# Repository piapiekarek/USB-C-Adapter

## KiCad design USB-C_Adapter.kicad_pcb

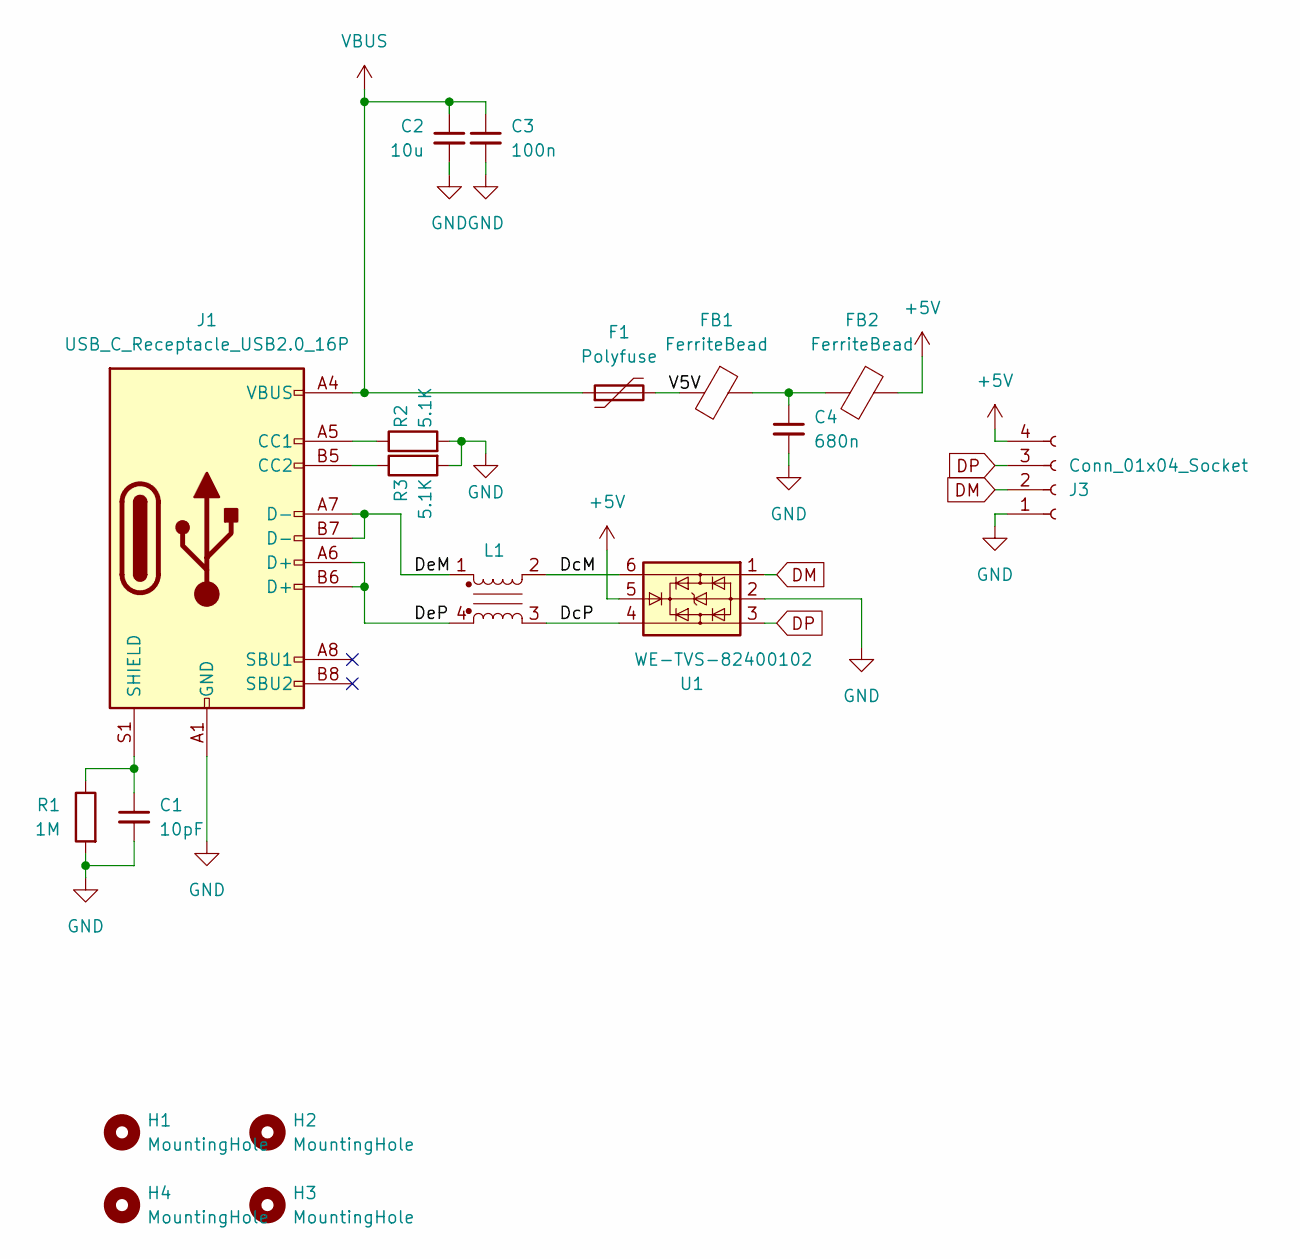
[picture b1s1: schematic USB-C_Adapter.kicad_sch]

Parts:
C1: 10pF; C_0402_1005Metric_Pad0.74x0.62mm_HandSolder
C2: 10u; C_0402_1005Metric_Pad0.74x0.62mm_HandSolder
C3: 100n; C_0402_1005Metric_Pad0.74x0.62mm_HandSolder
C4: 680n; C_0402_1005Metric_Pad0.74x0.62mm_HandSolder
F1: Polyfuse; C_0805_2012Metric_Pad1.18x1.45mm_HandSolder
FB1, FB2: FerriteBead; C_0201_0603Metric_Pad0.64x0.40mm_HandSolder
H1, H2, H3, H4: MountingHole; MountingHole_2.2mm_M2
J1: USB_C_Receptacle_USB2.0_16P; USB_C_Receptacle_Bottom_Up SMD
J3: Conn_01x04_Socket; JST_PH_S4B-PH-K_1x04_P2.00mm_Horizontal
L1: Choke_Wurth_WE-CNSW_744232090; L_CommonMode_Wurth_WE-CNSW-1206
R1: 1M; C_0402_1005Metric_Pad0.74x0.62mm_HandSolder
R2, R3: 5.1K; C_0402_1005Metric_Pad0.74x0.62mm_HandSolder
U1: WE-TVS-82400102; SOT-23-6

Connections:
+5V: FB2.1, J3.4, U1.5
/DcM: L1.2, U1.6
/DcP: L1.3, U1.4
/DeM: J1.A7 (D-), J1.B7 (D-), L1.1
/DeP: J1.A6 (D+), J1.B6 (D+), L1.4
/V5V: F1.2, FB1.2
DM: J3.2, U1.1
DP: J3.3, U1.3
GND: C1.2, C2.2, C3.2, C4.2, J1.A1 (GND), J1.A12 (GND), J1.B1 (GND), J1.B12 (GND), J3.1, R1.2, R2.2, R3.2, U1.2
unnamed: C4.1, FB1.1, FB2.2
unnamed: J1.A5 (CC1), R2.1
unnamed: J1.B5 (CC2), R3.1
unnamed: C1.1, J1.S1 (SHIELD), R1.1
VBUS: C2.1, C3.1, F1.1, J1.A4 (VBUS), J1.A9 (VBUS), J1.B4 (VBUS), J1.B9 (VBUS)

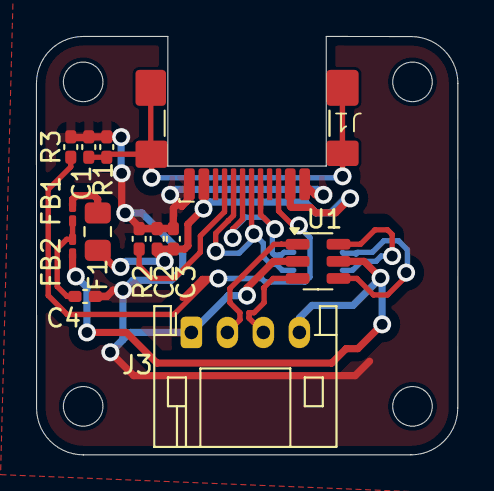
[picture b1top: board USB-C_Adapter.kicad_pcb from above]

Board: 2 copper layers, 23.4 x 23.2 mm, 18 parts (1 on the bottom side), 14 nets.

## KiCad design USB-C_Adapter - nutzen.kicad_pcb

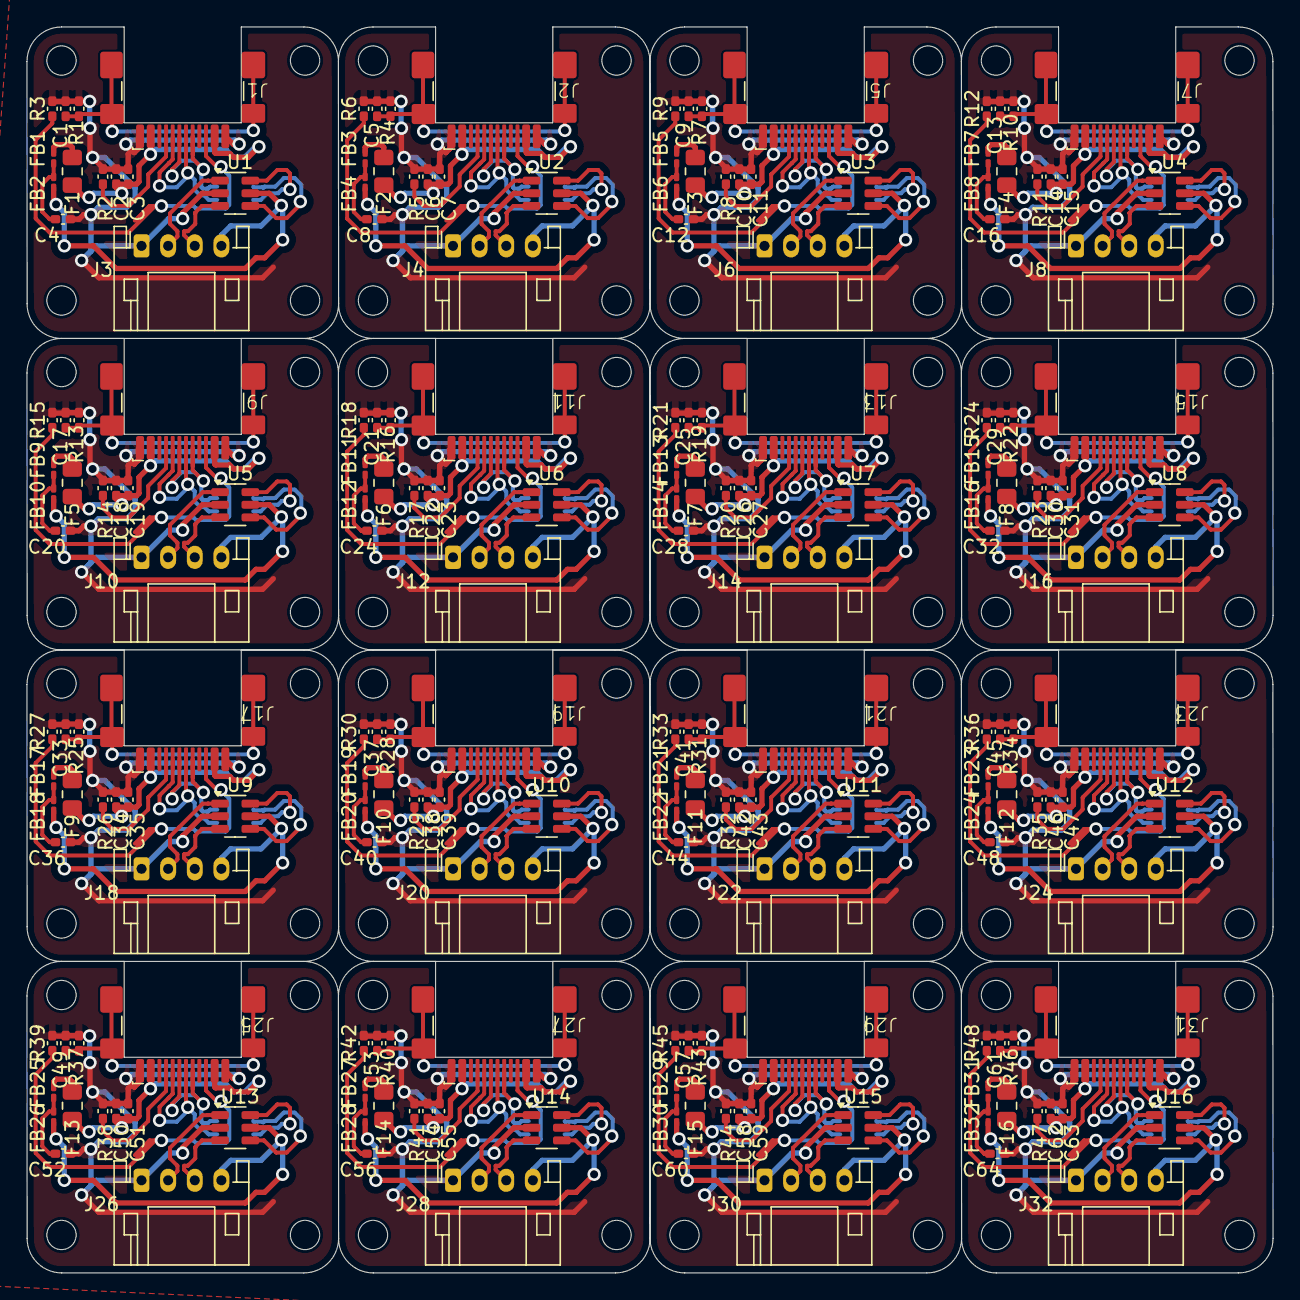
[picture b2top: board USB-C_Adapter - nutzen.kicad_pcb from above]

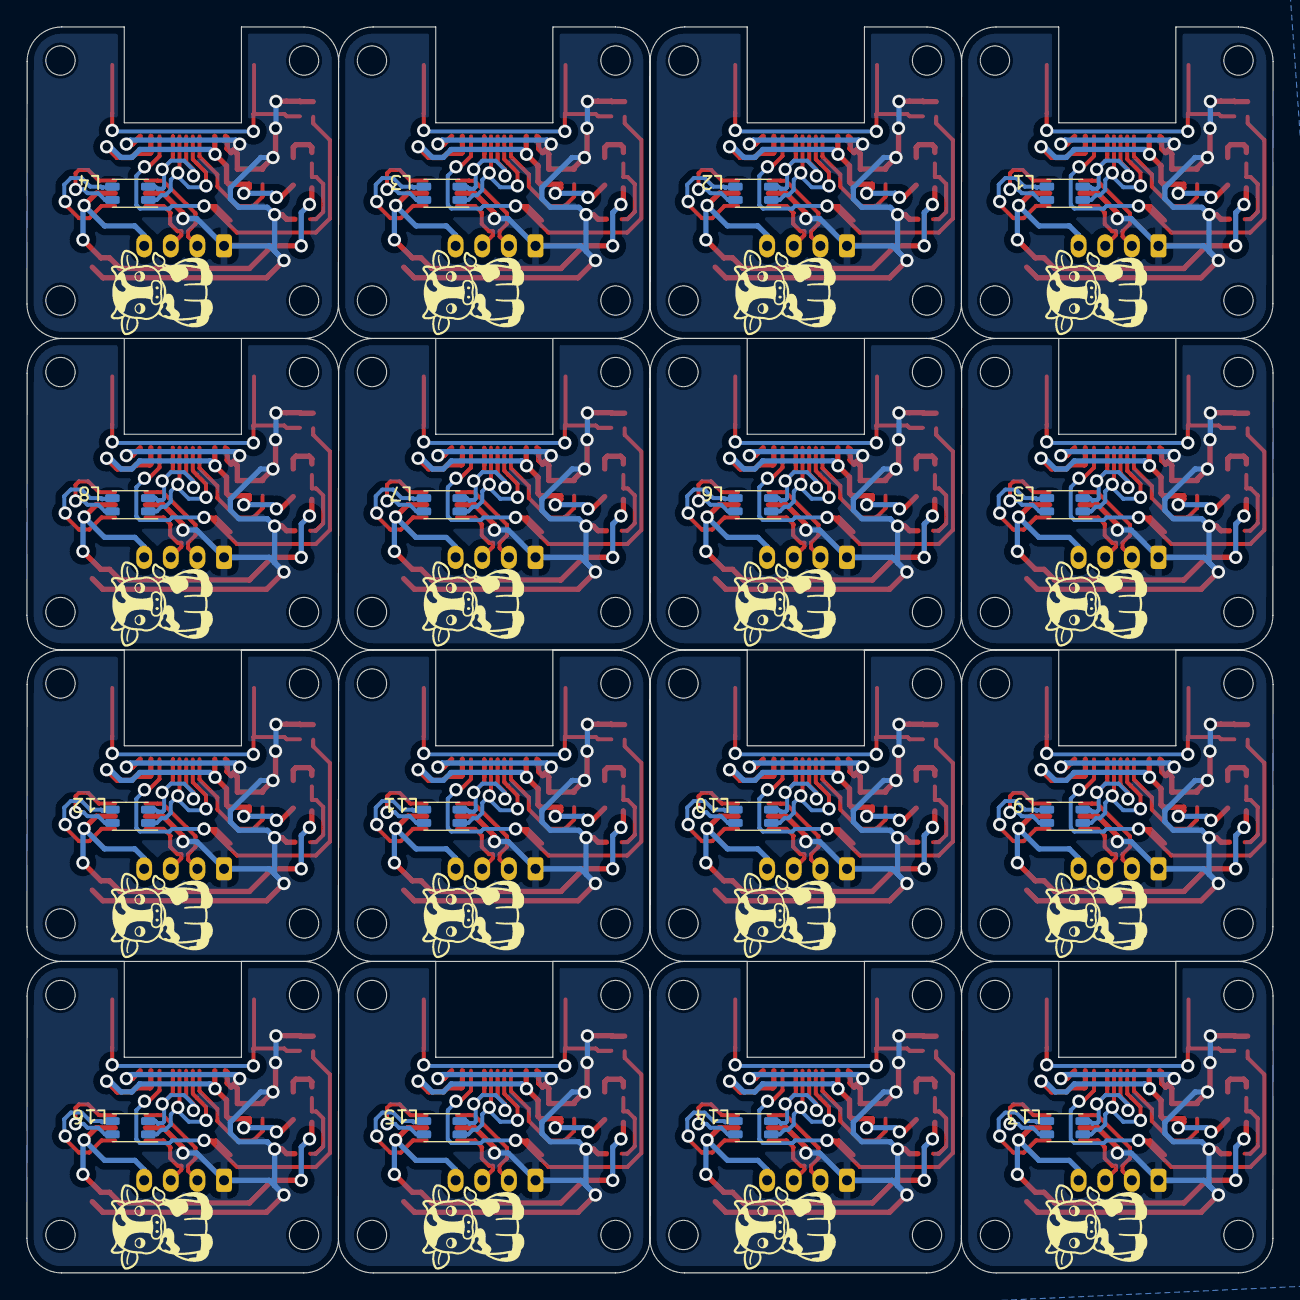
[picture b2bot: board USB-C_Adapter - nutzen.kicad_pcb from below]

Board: 2 copper layers, 93.6 x 93.6 mm, 288 parts (16 on the bottom side), 14 nets.

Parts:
C1, C5, C9, C13, C17, C21, C25, C29, C33, C37, C41, C45, C49, C53, C57, C61: 10pF; C_0402_1005Metric_Pad0.74x0.62mm_HandSolder
C2, C6, C10, C14, C18, C22, C26, C30, C34, C38, C42, C46, C50, C54, C58, C62: 10u; C_0402_1005Metric_Pad0.74x0.62mm_HandSolder
C3, C7, C11, C15, C19, C23, C27, C31, C35, C39, C43, C47, C51, C55, C59, C63: 100n; C_0402_1005Metric_Pad0.74x0.62mm_HandSolder
C4, C8, C12, C16, C20, C24, C28, C32, C36, C40, C44, C48, C52, C56, C60, C64: 680n; C_0402_1005Metric_Pad0.74x0.62mm_HandSolder
F1, F2, F3, F4, F5, F6, F7, F8, F9, F10, F11, F12, F13, F14, F15, F16: Polyfuse; C_0805_2012Metric_Pad1.18x1.45mm_HandSolder
FB1, FB2, FB3, FB4, FB5, FB6, FB7, FB8, FB9, FB10, FB11, FB12, FB13, FB14, FB15, FB16, FB17, FB18, FB19, FB20, FB21, FB22, FB23, FB24, FB25, FB26, FB27, FB28, FB29, FB30, FB31, FB32: FerriteBead; C_0201_0603Metric_Pad0.64x0.40mm_HandSolder
H1, H2, H3, H4, H5, H6, H7, H8, H9, H10, H11, H12, H13, H14, H15, H16, H17, H18, H19, H20, H21, H22, H23, H24, H25, H26, H27, H28, H29, H30, H31, H32, H33, H34, H35, H36, H37, H38, H39, H40, H41, H42, H43, H44, H45, H46, H47, H48, H49, H50, H51, H52, H53, H54, H55, H56, H57, H58, H59, H60, H61, H62, H63, H64: MountingHole; MountingHole_2.2mm_M2
J1, J2, J5, J7, J9, J11, J13, J15, J17, J19, J21, J23, J25, J27, J29, J31: USB_C_Receptacle_USB2.0_16P; USB_C_Receptacle_Bottom_Up SMD
J3, J4, J6, J8, J10, J12, J14, J16, J18, J20, J22, J24, J26, J28, J30, J32: Conn_01x04_Socket; JST_PH_S4B-PH-K_1x04_P2.00mm_Horizontal
L1, L2, L3, L4, L5, L6, L7, L8, L9, L10, L11, L12, L13, L14, L15, L16: Choke_Wurth_WE-CNSW_744232090; L_CommonMode_Wurth_WE-CNSW-1206
R1, R4, R7, R10, R13, R16, R19, R22, R25, R28, R31, R34, R37, R40, R43, R46: 1M; C_0402_1005Metric_Pad0.74x0.62mm_HandSolder
R2, R3, R5, R6, R8, R9, R11, R12, R14, R15, R17, R18, R20, R21, R23, R24, R26, R27, R29, R30, R32, R33, R35, R36, R38, R39, R41, R42, R44, R45, R47, R48: 5.1K; C_0402_1005Metric_Pad0.74x0.62mm_HandSolder
U1, U2, U3, U4, U5, U6, U7, U8, U9, U10, U11, U12, U13, U14, U15, U16: WE-TVS-82400102; SOT-23-6

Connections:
+5V: FB2.1, FB4.1, FB6.1, FB8.1, FB10.1, FB12.1, FB14.1, FB16.1, FB18.1, FB20.1, FB22.1, FB24.1, FB26.1, FB28.1, FB30.1, FB32.1, J3.4, J4.4, J6.4, J8.4, J10.4, J12.4, J14.4, J16.4, J18.4, J20.4, J22.4, J24.4, J26.4, J28.4, J30.4, J32.4, U1.5, U2.5, U3.5, U4.5, U5.5, U6.5, U7.5, U8.5, U9.5, U10.5, U11.5, U12.5, U13.5, U14.5, U15.5, U16.5
/DcM: L1.2, L2.2, L3.2, L4.2, L5.2, L6.2, L7.2, L8.2, L9.2, L10.2, L11.2, L12.2, L13.2, L14.2, L15.2, L16.2, U1.6, U2.6, U3.6, U4.6, U5.6, U6.6, U7.6, U8.6, U9.6, U10.6, U11.6, U12.6, U13.6, U14.6, U15.6, U16.6
/DcP: L1.3, L2.3, L3.3, L4.3, L5.3, L6.3, L7.3, L8.3, L9.3, L10.3, L11.3, L12.3, L13.3, L14.3, L15.3, L16.3, U1.4, U2.4, U3.4, U4.4, U5.4, U6.4, U7.4, U8.4, U9.4, U10.4, U11.4, U12.4, U13.4, U14.4, U15.4, U16.4
/DeM: J1.A7 (D-), J1.B7 (D-), J2.A7 (D-), J2.B7 (D-), J5.A7 (D-), J5.B7 (D-), J7.A7 (D-), J7.B7 (D-), J9.A7 (D-), J9.B7 (D-), J11.A7 (D-), J11.B7 (D-), J13.A7 (D-), J13.B7 (D-), J15.A7 (D-), J15.B7 (D-), J17.A7 (D-), J17.B7 (D-), J19.A7 (D-), J19.B7 (D-), J21.A7 (D-), J21.B7 (D-), J23.A7 (D-), J23.B7 (D-), J25.A7 (D-), J25.B7 (D-), J27.A7 (D-), J27.B7 (D-), J29.A7 (D-), J29.B7 (D-), J31.A7 (D-), J31.B7 (D-), L1.1, L2.1, L3.1, L4.1, L5.1, L6.1, L7.1, L8.1, L9.1, L10.1, L11.1, L12.1, L13.1, L14.1, L15.1, L16.1
/DeP: J1.A6 (D+), J1.B6 (D+), J2.A6 (D+), J2.B6 (D+), J5.A6 (D+), J5.B6 (D+), J7.A6 (D+), J7.B6 (D+), J9.A6 (D+), J9.B6 (D+), J11.A6 (D+), J11.B6 (D+), J13.A6 (D+), J13.B6 (D+), J15.A6 (D+), J15.B6 (D+), J17.A6 (D+), J17.B6 (D+), J19.A6 (D+), J19.B6 (D+), J21.A6 (D+), J21.B6 (D+), J23.A6 (D+), J23.B6 (D+), J25.A6 (D+), J25.B6 (D+), J27.A6 (D+), J27.B6 (D+), J29.A6 (D+), J29.B6 (D+), J31.A6 (D+), J31.B6 (D+), L1.4, L2.4, L3.4, L4.4, L5.4, L6.4, L7.4, L8.4, L9.4, L10.4, L11.4, L12.4, L13.4, L14.4, L15.4, L16.4
/V5V: F1.2, F2.2, F3.2, F4.2, F5.2, F6.2, F7.2, F8.2, F9.2, F10.2, F11.2, F12.2, F13.2, F14.2, F15.2, F16.2, FB1.2, FB3.2, FB5.2, FB7.2, FB9.2, FB11.2, FB13.2, FB15.2, FB17.2, FB19.2, FB21.2, FB23.2, FB25.2, FB27.2, FB29.2, FB31.2
DM: J3.2, J4.2, J6.2, J8.2, J10.2, J12.2, J14.2, J16.2, J18.2, J20.2, J22.2, J24.2, J26.2, J28.2, J30.2, J32.2, U1.1, U2.1, U3.1, U4.1, U5.1, U6.1, U7.1, U8.1, U9.1, U10.1, U11.1, U12.1, U13.1, U14.1, U15.1, U16.1
DP: J3.3, J4.3, J6.3, J8.3, J10.3, J12.3, J14.3, J16.3, J18.3, J20.3, J22.3, J24.3, J26.3, J28.3, J30.3, J32.3, U1.3, U2.3, U3.3, U4.3, U5.3, U6.3, U7.3, U8.3, U9.3, U10.3, U11.3, U12.3, U13.3, U14.3, U15.3, U16.3
GND: C1.2, C2.2, C3.2, C4.2, C5.2, C6.2, C7.2, C8.2, C9.2, C10.2, C11.2, C12.2, C13.2, C14.2, C15.2, C16.2, C17.2, C18.2, C19.2, C20.2, C21.2, C22.2, C23.2, C24.2, C25.2, C26.2, C27.2, C28.2, C29.2, C30.2, C31.2, C32.2, C33.2, C34.2, C35.2, C36.2, C37.2, C38.2, C39.2, C40.2, C41.2, C42.2, C43.2, C44.2, C45.2, C46.2, C47.2, C48.2, C49.2, C50.2, C51.2, C52.2, C53.2, C54.2, C55.2, C56.2, C57.2, C58.2, C59.2, C60.2, C61.2, C62.2, C63.2, C64.2, J1.A1 (GND), J1.A12 (GND), J1.B1 (GND), J1.B12 (GND), J2.A1 (GND), J2.A12 (GND), J2.B1 (GND), J2.B12 (GND), J3.1, J4.1, J5.A1 (GND), J5.A12 (GND), J5.B1 (GND), J5.B12 (GND), J6.1, J7.A1 (GND), J7.A12 (GND), J7.B1 (GND), J7.B12 (GND), J8.1, J9.A1 (GND), J9.A12 (GND), J9.B1 (GND), J9.B12 (GND), J10.1, J11.A1 (GND), J11.A12 (GND), J11.B1 (GND), J11.B12 (GND), J12.1, J13.A1 (GND), J13.A12 (GND), J13.B1 (GND), J13.B12 (GND), J14.1, J15.A1 (GND), J15.A12 (GND), J15.B1 (GND), J15.B12 (GND), J16.1, J17.A1 (GND), J17.A12 (GND), J17.B1 (GND), J17.B12 (GND), J18.1, J19.A1 (GND), J19.A12 (GND), J19.B1 (GND), J19.B12 (GND), J20.1, J21.A1 (GND), J21.A12 (GND), J21.B1 (GND), J21.B12 (GND), J22.1, J23.A1 (GND), J23.A12 (GND), J23.B1 (GND), J23.B12 (GND), J24.1, J25.A1 (GND), J25.A12 (GND), J25.B1 (GND), J25.B12 (GND), J26.1, J27.A1 (GND), J27.A12 (GND), J27.B1 (GND), J27.B12 (GND), J28.1, J29.A1 (GND), J29.A12 (GND), J29.B1 (GND), J29.B12 (GND), J30.1, J31.A1 (GND), J31.A12 (GND), J31.B1 (GND), J31.B12 (GND), J32.1, R1.2, R2.2, R3.2, R4.2, R5.2, R6.2, R7.2, R8.2, R9.2, R10.2, R11.2, R12.2, R13.2, R14.2, R15.2, R16.2, R17.2, R18.2, R19.2, R20.2, R21.2, R22.2, R23.2, R24.2, R25.2, R26.2, R27.2, R28.2, R29.2, R30.2, R31.2, R32.2, R33.2, R34.2, R35.2, R36.2, R37.2, R38.2, R39.2, R40.2, R41.2, R42.2, R43.2, R44.2, R45.2, R46.2, R47.2, R48.2, U1.2, U2.2, U3.2, U4.2, U5.2, U6.2, U7.2, U8.2, U9.2, U10.2, U11.2, U12.2, U13.2, U14.2, U15.2, U16.2
unnamed: C4.1, C8.1, C12.1, C16.1, C20.1, C24.1, C28.1, C32.1, C36.1, C40.1, C44.1, C48.1, C52.1, C56.1, C60.1, C64.1, FB1.1, FB2.2, FB3.1, FB4.2, FB5.1, FB6.2, FB7.1, FB8.2, FB9.1, FB10.2, FB11.1, FB12.2, FB13.1, FB14.2, FB15.1, FB16.2, FB17.1, FB18.2, FB19.1, FB20.2, FB21.1, FB22.2, FB23.1, FB24.2, FB25.1, FB26.2, FB27.1, FB28.2, FB29.1, FB30.2, FB31.1, FB32.2
unnamed: J1.A5 (CC1), J2.A5 (CC1), J5.A5 (CC1), J7.A5 (CC1), J9.A5 (CC1), J11.A5 (CC1), J13.A5 (CC1), J15.A5 (CC1), J17.A5 (CC1), J19.A5 (CC1), J21.A5 (CC1), J23.A5 (CC1), J25.A5 (CC1), J27.A5 (CC1), J29.A5 (CC1), J31.A5 (CC1), R2.1, R5.1, R8.1, R11.1, R14.1, R17.1, R20.1, R23.1, R26.1, R29.1, R32.1, R35.1, R38.1, R41.1, R44.1, R47.1
unnamed: J1.B5 (CC2), J2.B5 (CC2), J5.B5 (CC2), J7.B5 (CC2), J9.B5 (CC2), J11.B5 (CC2), J13.B5 (CC2), J15.B5 (CC2), J17.B5 (CC2), J19.B5 (CC2), J21.B5 (CC2), J23.B5 (CC2), J25.B5 (CC2), J27.B5 (CC2), J29.B5 (CC2), J31.B5 (CC2), R3.1, R6.1, R9.1, R12.1, R15.1, R18.1, R21.1, R24.1, R27.1, R30.1, R33.1, R36.1, R39.1, R42.1, R45.1, R48.1
unnamed: C1.1, C5.1, C9.1, C13.1, C17.1, C21.1, C25.1, C29.1, C33.1, C37.1, C41.1, C45.1, C49.1, C53.1, C57.1, C61.1, J1.S1 (SHIELD), J2.S1 (SHIELD), J5.S1 (SHIELD), J7.S1 (SHIELD), J9.S1 (SHIELD), J11.S1 (SHIELD), J13.S1 (SHIELD), J15.S1 (SHIELD), J17.S1 (SHIELD), J19.S1 (SHIELD), J21.S1 (SHIELD), J23.S1 (SHIELD), J25.S1 (SHIELD), J27.S1 (SHIELD), J29.S1 (SHIELD), J31.S1 (SHIELD), R1.1, R4.1, R7.1, R10.1, R13.1, R16.1, R19.1, R22.1, R25.1, R28.1, R31.1, R34.1, R37.1, R40.1, R43.1, R46.1
VBUS: C2.1, C3.1, C6.1, C7.1, C10.1, C11.1, C14.1, C15.1, C18.1, C19.1, C22.1, C23.1, C26.1, C27.1, C30.1, C31.1, C34.1, C35.1, C38.1, C39.1, C42.1, C43.1, C46.1, C47.1, C50.1, C51.1, C54.1, C55.1, C58.1, C59.1, C62.1, C63.1, F1.1, F2.1, F3.1, F4.1, F5.1, F6.1, F7.1, F8.1, F9.1, F10.1, F11.1, F12.1, F13.1, F14.1, F15.1, F16.1, J1.A4 (VBUS), J1.A9 (VBUS), J1.B4 (VBUS), J1.B9 (VBUS), J2.A4 (VBUS), J2.A9 (VBUS), J2.B4 (VBUS), J2.B9 (VBUS), J5.A4 (VBUS), J5.A9 (VBUS), J5.B4 (VBUS), J5.B9 (VBUS), J7.A4 (VBUS), J7.A9 (VBUS), J7.B4 (VBUS), J7.B9 (VBUS), J9.A4 (VBUS), J9.A9 (VBUS), J9.B4 (VBUS), J9.B9 (VBUS), J11.A4 (VBUS), J11.A9 (VBUS), J11.B4 (VBUS), J11.B9 (VBUS), J13.A4 (VBUS), J13.A9 (VBUS), J13.B4 (VBUS), J13.B9 (VBUS), J15.A4 (VBUS), J15.A9 (VBUS), J15.B4 (VBUS), J15.B9 (VBUS), J17.A4 (VBUS), J17.A9 (VBUS), J17.B4 (VBUS), J17.B9 (VBUS), J19.A4 (VBUS), J19.A9 (VBUS), J19.B4 (VBUS), J19.B9 (VBUS), J21.A4 (VBUS), J21.A9 (VBUS), J21.B4 (VBUS), J21.B9 (VBUS), J23.A4 (VBUS), J23.A9 (VBUS), J23.B4 (VBUS), J23.B9 (VBUS), J25.A4 (VBUS), J25.A9 (VBUS), J25.B4 (VBUS), J25.B9 (VBUS), J27.A4 (VBUS), J27.A9 (VBUS), J27.B4 (VBUS), J27.B9 (VBUS), J29.A4 (VBUS), J29.A9 (VBUS), J29.B4 (VBUS), J29.B9 (VBUS), J31.A4 (VBUS), J31.A9 (VBUS), J31.B4 (VBUS), J31.B9 (VBUS)

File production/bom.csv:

Designator,Footprint,Quantity,Value,LCSC Part #
"C1, C13, C17, C21, C25, C29, C33, C37, C41, C45, C49, C5, C53, C57, C61, C9",0402,16,10pF,
"C10, C14, C18, C2, C22, C26, C30, C34, C38, C42, C46, C50, C54, C58, C6, C62",0402,16,10u,
"C11, C15, C19, C23, C27, C3, C31, C35, C39, C43, C47, C51, C55, C59, C63, C7",0402,16,100n,
"C12, C16, C20, C24, C28, C32, C36, C4, C40, C44, C48, C52, C56, C60, C64, C8",0402,16,680n,
"F1, F10, F11, F12, F13, F14, F15, F16, F2, F3, F4, F5, F6, F7, F8, F9",0805,16,Polyfuse,
"FB1, FB10, FB11, FB12, FB13, FB14, FB15, FB16, FB17, FB18, FB19, FB2, FB20, FB21, FB22, FB23, FB24, FB25, FB26, FB27, FB28, FB29, FB3, FB30, FB31, FB32, FB4, FB5, FB6, FB7, FB8, FB9",0201,32,FerriteBead,
"J1, J11, J13, J15, J17, J19, J2, J21, J23, J25, J27, J29, J31, J5, J7, J9",USB_C_Receptacle_Bottom_Up SMD,16,USB_C_Receptacle_USB2.0_16P,
"J10, J12, J14, J16, J18, J20, J22, J24, J26, J28, J3, J30, J32, J4, J6, J8",JST_PH_S4B-PH-K_1x04_P2.00mm_Horizontal,16,Conn_01x04_Socket,
"L1, L10, L11, L12, L13, L14, L15, L16, L2, L3, L4, L5, L6, L7, L8, L9",L_CommonMode_Wurth_WE-CNSW-1206,16,Choke_Wurth_WE-CNSW_744232090,
"R1, R10, R13, R16, R19, R22, R25, R28, R31, R34, R37, R4, R40, R43, R46, R7",0402,16,1M,
"R11, R12, R14, R15, R17, R18, R2, R20, R21, R23, R24, R26, R27, R29, R3, R30, R32, R33, R35, R36, R38, R39, R41, R42, R44, R45, R47, R48, R5, R6, R8, R9",0402,32,5.1K,
"U1, U10, U11, U12, U13, U14, U15, U16, U2, U3, U4, U5, U6, U7, U8, U9",SOT-23-6,16,WE-TVS-82400102,

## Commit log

2024-11-19 final design
